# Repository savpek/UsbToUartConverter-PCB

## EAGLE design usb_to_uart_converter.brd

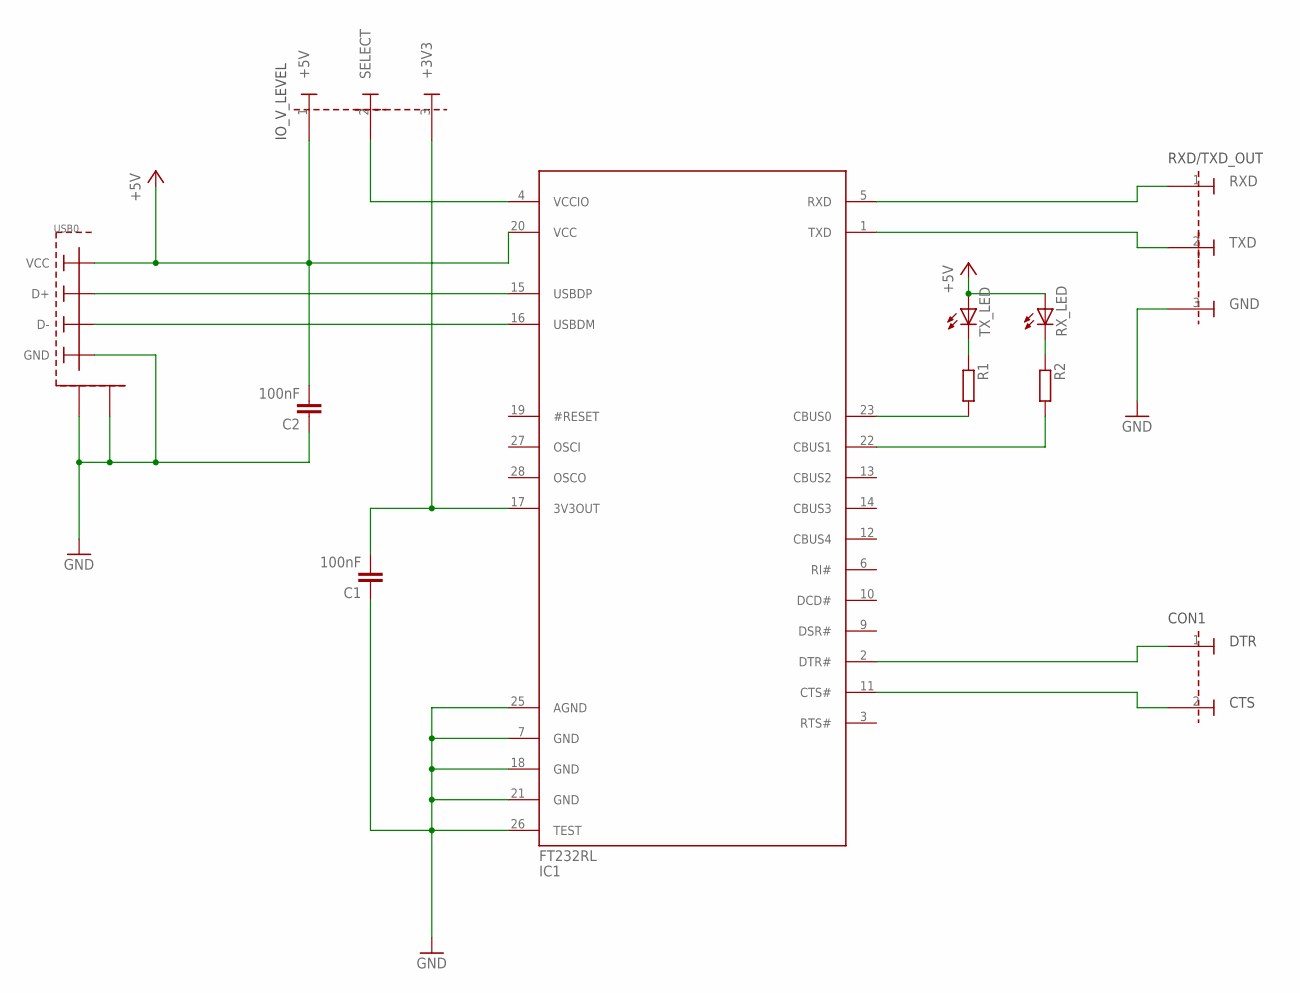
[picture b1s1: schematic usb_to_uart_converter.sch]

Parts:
C1, C2: 100nF; C0805
CON1: CONNECTOR_2PIN1X2; 1X2_GENERIC
IC1: FT232RL; SSOP28
IO_V_LEVEL: CONNECTOR_3PINWITH_LABELS; 1X3_GENERIC_WITH_LABELS
R1, R2: R-EU_R0805; R0805
RXD/TXD_OUT: CONNECTOR_3PINWITH_LABELS; 1X3_GENERIC_WITH_LABELS
RX_LED: LED_LIBCHIPLED_0805; CHIPLED_0805
TX_LED: LED_LIBCHIPLED_0805; CHIPLED_0805
USB0: USB-BWUERTH-ELECTRONIC-USB-B; USB-B-THROUGH-HOLE

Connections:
+5V: C2.2, IC1.20 (VCC), IO_V_LEVEL.1, RX_LED.A, TX_LED.A, USB0.VCC
GND: C1.1, C2.1, IC1.7 (GND), IC1.18 (GND), IC1.21 (GND), IC1.25 (AGND), IC1.26 (TEST), RXD/TXD_OUT.3, USB0.GND, USB0.SHIELD, USB0.SHIELD@2 (SHIELD)
unnamed: IC1.15 (USBDP), USB0.D+
unnamed: IC1.16 (USBDM), USB0.D-
unnamed: C1.2, IC1.17 (3V3OUT), IO_V_LEVEL.3
unnamed: IC1.4 (VCCIO), IO_V_LEVEL.2
unnamed: IC1.5 (RXD), RXD/TXD_OUT.1
unnamed: IC1.1 (TXD), RXD/TXD_OUT.2
unnamed: R1.1, TX_LED.C
unnamed: R2.1, RX_LED.C
unnamed: IC1.23 (CBUS0), R1.2
unnamed: IC1.22 (CBUS1), R2.2
unnamed: CON1.1, IC1.2 (DTR#)
unnamed: CON1.2, IC1.11 (CTS#)

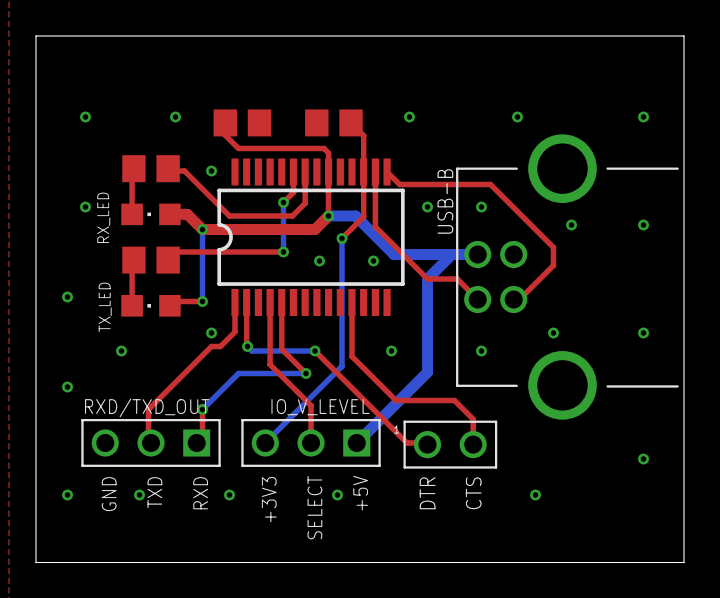
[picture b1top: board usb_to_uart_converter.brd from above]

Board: 2 copper layers, 36.0 x 29.2 mm, 11 parts (0 on the bottom side), 14 nets.

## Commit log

2012-04-17 First version. Design sended to iTeadStudios.
2012-07-25 Opened project and project file updated at same time.
